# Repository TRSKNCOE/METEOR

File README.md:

# METEOR
Node-MCU based robot which works on android application with multiple modes such as line tracing,gyroscope,voice control and manual mode.  
It has real time obstacle avoiding sensor integrated with it.

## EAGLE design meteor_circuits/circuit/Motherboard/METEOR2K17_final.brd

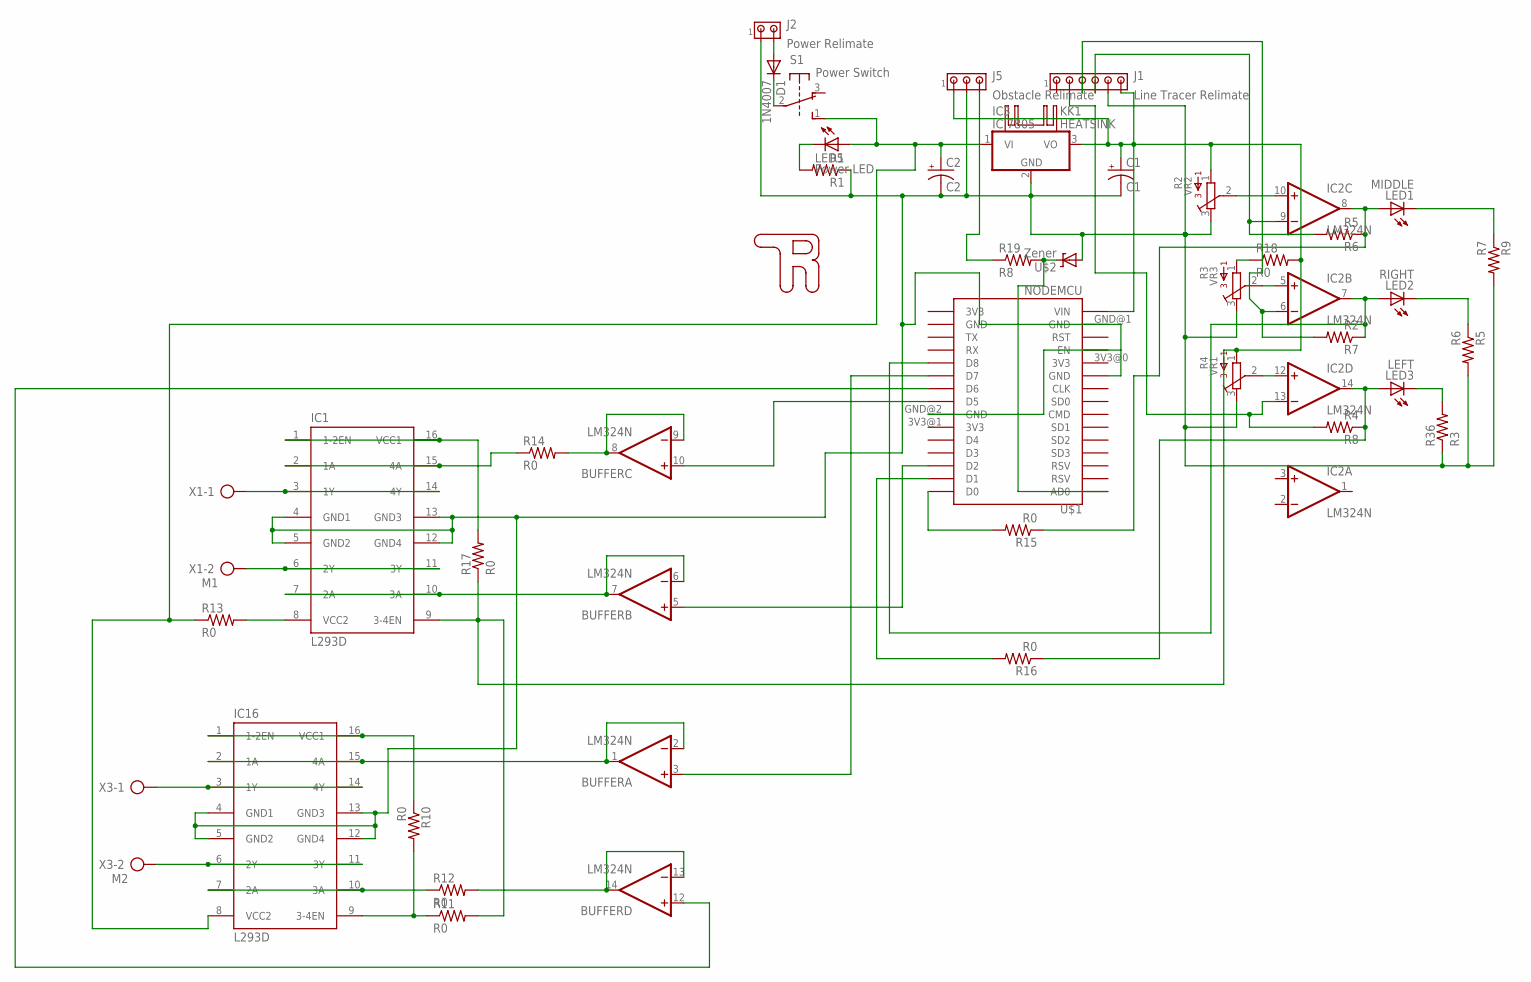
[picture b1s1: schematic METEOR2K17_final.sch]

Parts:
BUFFER: LM324N; DIL14
C1: C1; CPOL-RADIAL-5MM-10MM
C2: C2; E3,5-8
D1: 1N4007; DO41-10
IC1, IC16: L293D; DIL16
IC2: LM324N; DIL14
IC3: IC 7805; TO220V
J1: Line Tracer Relimate; 10X06MTA
J2: Power Relimate; 10X02MTA
J5: Obstacle Relimate; 10X03MTA
KK1: HEATSINK
LED1: MIDDLE; LED3MM
LED2: RIGHT; LED3MM
LED3: LEFT; LED3MM
LED5: Power LED; LED3MM
R1: R1; 0204/7
R2: VR2; 3386W
R3: VR3; 3386W
R4: VR1; 3386W
R5: R6; 0204/7
R6: R5; 0204/7
R7: R2; 0204/7
R8: R4; 0204/7
R9: R7; 0204/7
R10, R11, R13, R15, R16, R17, R18: R0; 0204/7
R12: R0; 0207/10
R14: R0; 0207/12
R19: R8; 0204/7
R36: R3; 0204/7
S1: Power Switch; 9077-2
U$1: NODEMCU; NODEMCU_HSILK
U$2: Zener; DIODE-ZENER
U$3: TRLOGO
X1: M1; AK300/2
X3: M2; AK300/2

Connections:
5V: BUFFER.4 (V+), C1.+, IC1.1 (1-2EN), IC1.9 (3-4EN), IC1.16 (VCC1), IC2.4 (V+), IC3.3 (VO), IC16.1 (1-2EN), IC16.9 (3-4EN), IC16.16 (VCC1), J1.1 (6), J5.1, R2.1, R4.1, R10.1, R10.2, R11.1, R11.2, R17.1, R17.2, R18.2, U$1.VIN
12V: C2.+, IC1.8 (VCC2), IC3.1 (VI), IC16.8 (VCC2), LED5.A, R13.1, R13.2, S1.1 (S)
-LED3: LED3.K (C), R36.2
GND: BUFFER.11 (V-), C1.-, C2.-, IC1.4 (GND1), IC1.5 (GND2), IC1.12 (GND4), IC1.13 (GND3), IC2.11 (V-), IC3.2 (GND), IC16.4 (GND1), IC16.5 (GND2), IC16.12 (GND4), IC16.13 (GND3), J1.2 (5), J2.1, J5.2, R1.1, R2.3, R3.3, R4.3, R5.2, R9.2, R36.1, U$1.GND@0 (GND), U$1.GND@2 (GND), U$2.P$2 (A)
unnamed: IC2.6 (-IN), J1.4 (3), R7.2
unnamed: D1.A, J2.2
unnamed: IC2.12 (+IN), R4.2
unnamed: J5.3, R19.1
unnamed: IC2.7 (OUT), LED2.A, R7.1, U$1.D8
unnamed: LED5.K (C), R1.2
unnamed: IC1.2 (1A), IC1.15 (4A), R14.1
unnamed: IC2.14 (OUT), LED3.A, R8.1, R16.1
unnamed: IC1.3 (1Y), IC1.14 (4Y), X1.1
unnamed: IC1.6 (2Y), IC1.11 (3Y), X1.2
unnamed: D1.C, S1.2
unnamed: R3.1, R18.1
unnamed: BUFFER.6 (-IN), BUFFER.7 (OUT), IC1.7 (2A), IC1.10 (3A)
unnamed: IC2.8 (OUT), LED1.A, R6.1, R15.1
unnamed: R19.2, U$1.AD0, U$2.P$1 (C)
unnamed: BUFFER.13 (-IN), BUFFER.14 (OUT), R12.2
unnamed: IC2.10 (+IN), R2.2
unnamed: BUFFER.10 (+IN), U$1.D5
unnamed: IC2.5 (+IN), R3.2
unnamed: BUFFER.5 (+IN), U$1.D2
unnamed: BUFFER.3 (+IN), U$1.D7
unnamed: IC16.7 (2A), IC16.10 (3A), R12.1
unnamed: IC2.9 (-IN), J1.3 (4), R6.2
unnamed: IC2.13 (-IN), J1.5 (2), R8.2
unnamed: LED1.K (C), R9.1
unnamed: LED2.K (C), R5.1
unnamed: BUFFER.8 (OUT), BUFFER.9 (-IN), R14.2
unnamed: IC16.3 (1Y), IC16.14 (4Y), X3.1
unnamed: BUFFER.12 (+IN), U$1.D6
unnamed: BUFFER.1 (OUT), BUFFER.2 (-IN), IC16.2 (1A), IC16.15 (4A)
unnamed: IC16.6 (2Y), IC16.11 (3Y), X3.2
unnamed: R15.2, U$1.D0
unnamed: R16.2, U$1.D1

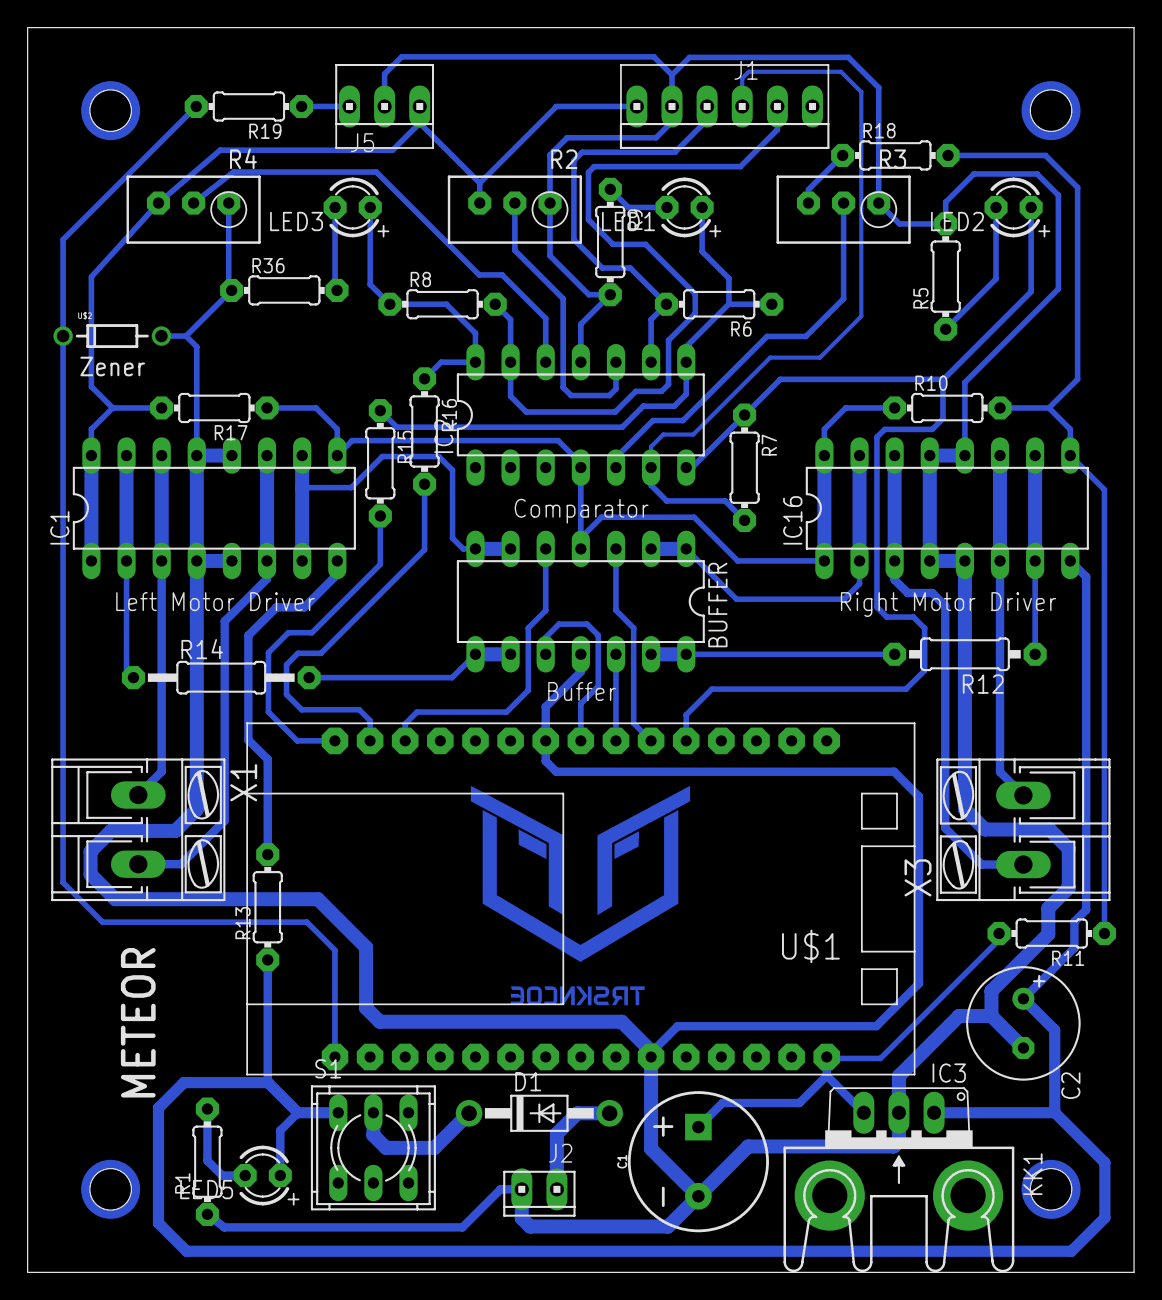
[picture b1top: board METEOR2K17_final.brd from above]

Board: 2 copper layers, 80.0 x 90.0 mm, 42 parts (0 on the bottom side), 37 nets.

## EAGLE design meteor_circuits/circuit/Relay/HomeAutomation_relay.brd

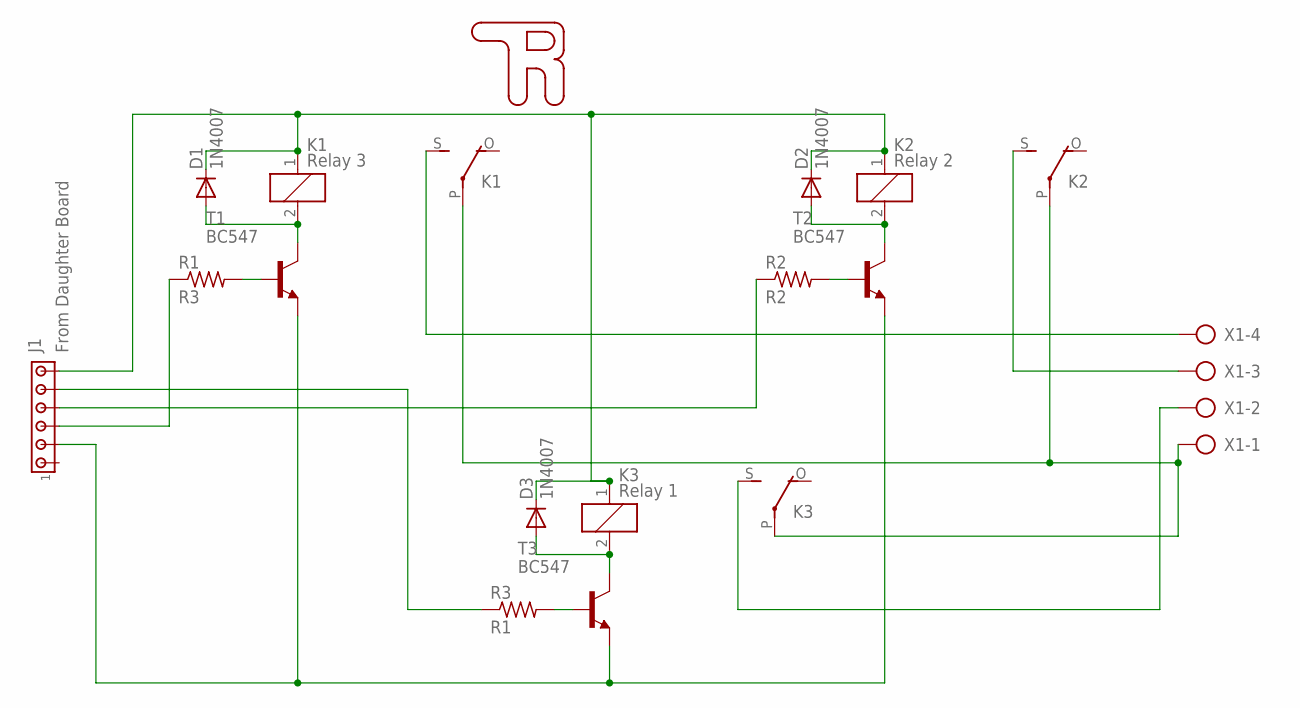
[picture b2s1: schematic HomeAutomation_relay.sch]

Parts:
D1, D2, D3: 1N4007; DO41-10
J1: From Daughter Board; 10X06MTA
K1: Relay 3; G5LE
K2: Relay 2; G5LE
K3: Relay 1; G5LE
R1: R3; 0204/7
R2: R2; 0204/7
R3: R1; 0204/7
T1, T2, T3: BC547; TO92
U$1: TRLOGO1; TRLOGO_14
X1: AK300/4

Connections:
unnamed: J1.2, T1.1 (E), T2.1 (E), T3.1 (E)
unnamed: D2.A, K2.2, T2.3 (C)
unnamed: D1.A, K1.2, T1.3 (C)
unnamed: D3.A, K3.2, T3.3 (C)
unnamed: D1.C, D2.C, D3.C, J1.6, K1.1, K2.1, K3.1
unnamed: K1.P, K2.P, K3.P, X1.1
unnamed: K3.S, X1.2
unnamed: K1.S, X1.4
unnamed: K2.S, X1.3
unnamed: R1.2, T1.2 (B)
unnamed: J1.3, R1.1
unnamed: J1.4, R2.1
unnamed: R2.2, T2.2 (B)
unnamed: R3.2, T3.2 (B)
unnamed: J1.5, R3.1

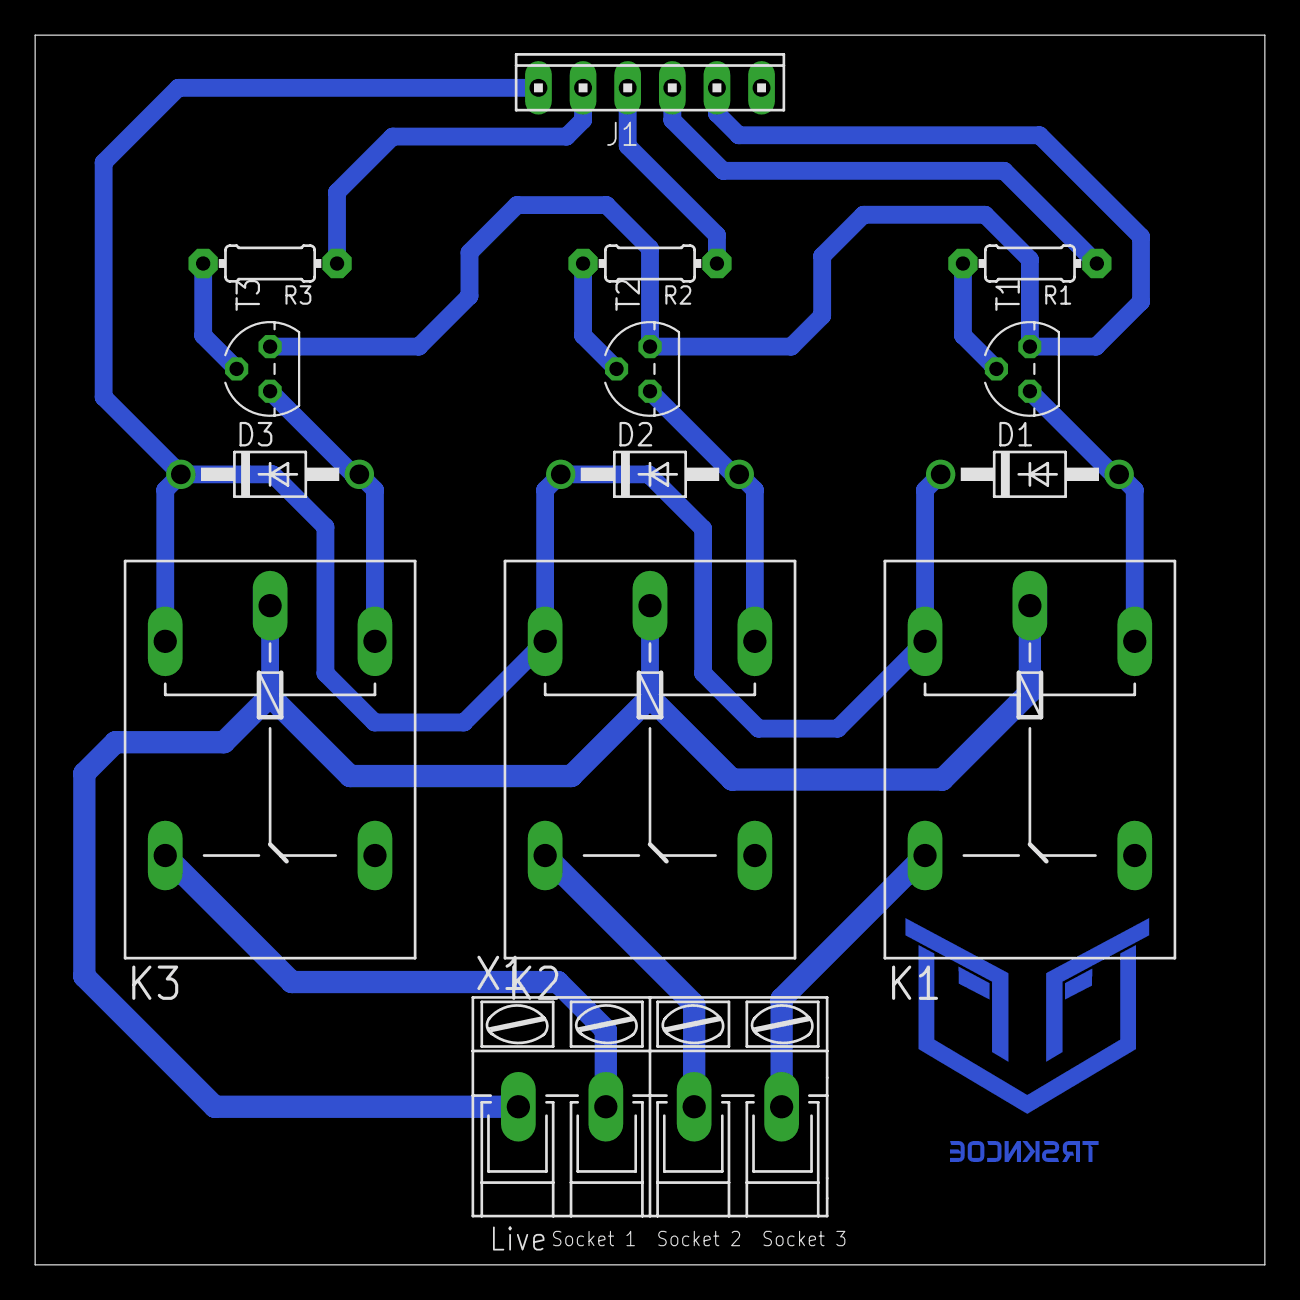
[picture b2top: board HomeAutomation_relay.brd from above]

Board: 2 copper layers, 70.0 x 70.0 mm, 15 parts (0 on the bottom side), 15 nets.

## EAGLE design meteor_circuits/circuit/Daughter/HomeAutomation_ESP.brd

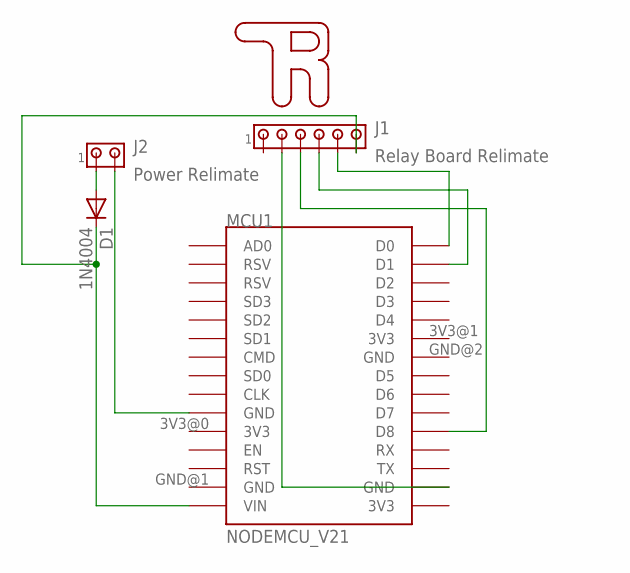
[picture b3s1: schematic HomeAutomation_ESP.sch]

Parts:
D1: 1N4004; DO41-10
J1: Relay Board Relimate; 10X06MTA
J2: Power Relimate; 10X02MTA
MCU1: NODEMCU_V21; NODEMCU_NOSILK
U$1: TRLOGO2; TRLOGO_6.4

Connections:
5V: D1.C, J1.6, MCU1.VIN
5V@0: D1.A, J2.1
GND@0: J2.2, MCU1.GND@0 (GND)
GND@1: J1.2, MCU1.GND@3 (GND)
R1: J1.5, MCU1.D0
R2: J1.4, MCU1.D1
R3: J1.3, MCU1.D8

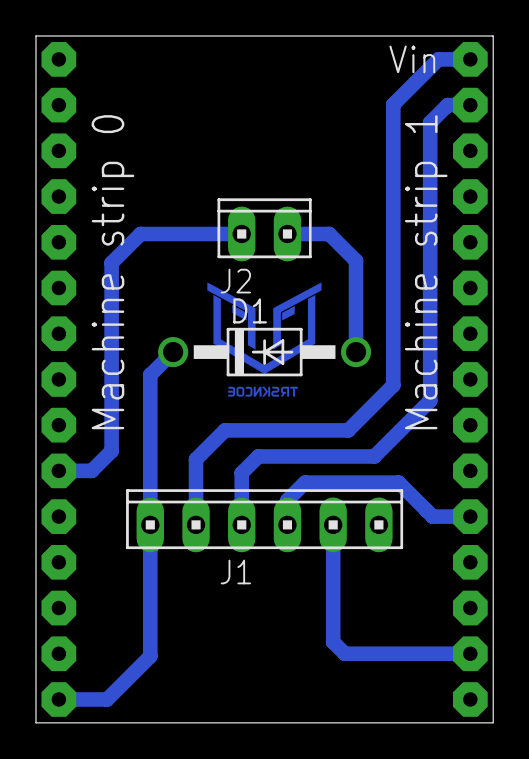
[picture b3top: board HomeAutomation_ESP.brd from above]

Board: 2 copper layers, 25.4 x 38.2 mm, 5 parts (0 on the bottom side), 7 nets.

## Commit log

2022-12-08 meteor 2017 data
2023-09-16 Add files via upload
    Old Meteor ATMEGA 8 Based robot code

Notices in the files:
parts and their libraries:
SparkFun-Capacitors: Licensing: Creative Commons ShareAlike 4.0 International - https://creativecommons.org/licenses/by-sa/4.0
heatsink: Copyright (C) 2004, Bob Starr (bobstarr@mindspring.com)
